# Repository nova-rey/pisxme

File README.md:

# PiSXMe

PiSXMe is an open-hardware compute-appliance carrier project for a Raspberry Pi Compute Module 5 and an NVIDIA Tesla V100 SXM2 module.

This public repository is a recovery/preservation snapshot prepared from verified local source files while the original iCloud-backed checkout contained unavailable File Provider placeholders. It preserves the Rev A design evidence and handoff material; it is not a claim that Rev A is fabrication-ready.

Read [HANDOFF_LINUX_WORKSTATION.md](HANDOFF_LINUX_WORKSTATION.md), [TOOLING_STATUS.md](TOOLING_STATUS.md), [references/REFERENCE_INDEX.md](references/REFERENCE_INDEX.md), and [plans/M6_LINUX_RESTART_CHECKLIST.md](plans/M6_LINUX_RESTART_CHECKLIST.md) before changing the design.

The authoritative active-design hashes and unavailable-source manifest are recorded in [RECOVERY_MANIFEST.md](RECOVERY_MANIFEST.md).

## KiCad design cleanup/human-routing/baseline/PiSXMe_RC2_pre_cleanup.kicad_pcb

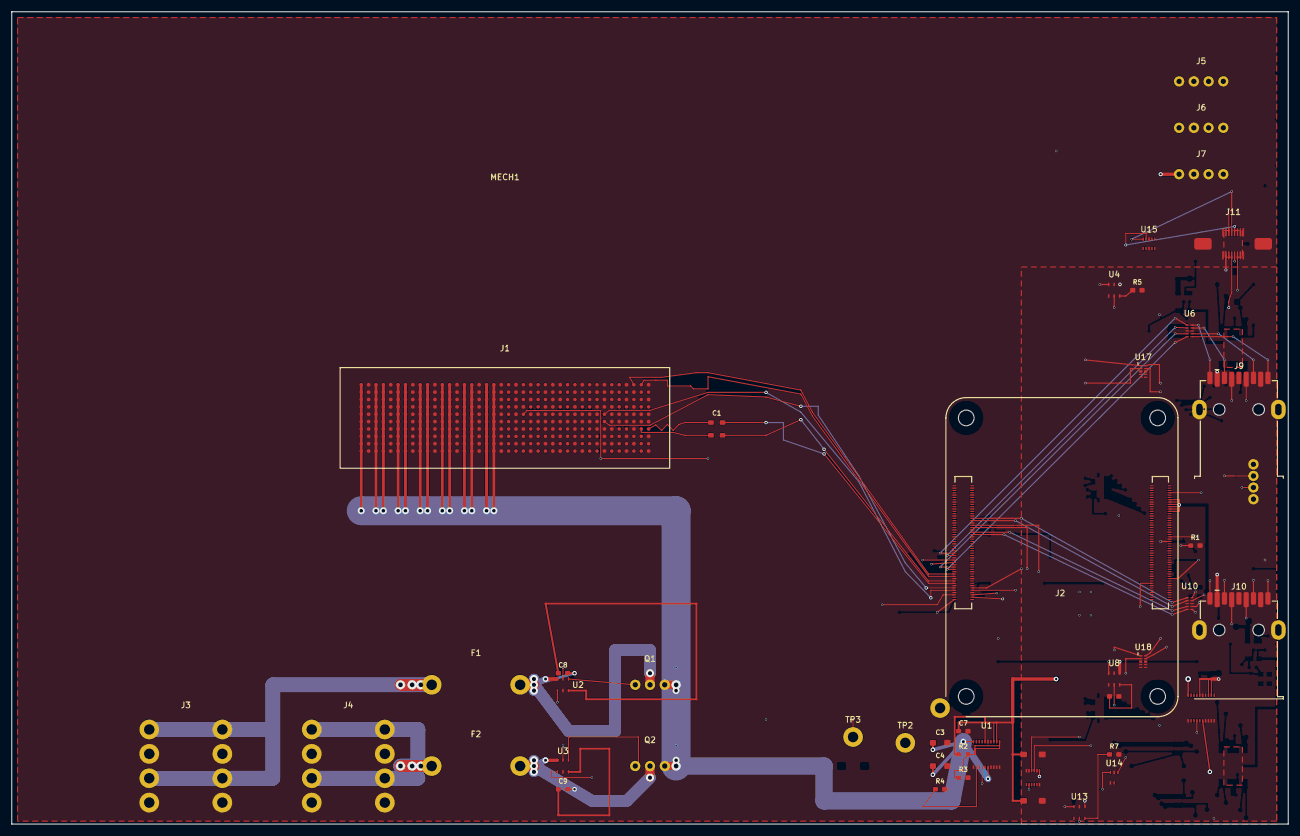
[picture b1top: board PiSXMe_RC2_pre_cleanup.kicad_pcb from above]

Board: 6 copper layers, 220.0 x 140.0 mm, 49 parts (0 on the bottom side), 56 nets.

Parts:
C1, C2: GRM21BR71H224KA01# 220nF; ROUT_0805
C3, C4: 10uF 50V buck input; ROUT_1206
C5, C6: 22uF 25V buck output; ROUT_1210
C7: 100nF VLDOIN; ROUT_0603
C8: 100nF LM74700 VCAP A; ROUT_0603
C9: 100nF LM74700 VCAP B; ROUT_0603
F1, F2: Littelfuse 178.6165.0001 / 0297015.U 15A holder; ATO_FuseHolder
J1: 74221-101LF; SXM2_74221-101LF
J2: 2x 10164227-1004A1RLF; CM5_1004
J3, J4: Molex 39301082 / Mini-Fit Jr 8-circuit; MiniFitJr_8_RA
J5: Molex 22-23-2041 / PC PWM fan 1; Fan_2x2_2.54mm
J6: Molex 22-23-2041 / PC PWM fan 2; Fan_2x2_2.54mm
J7: Molex 22-23-2041 / pump or auxiliary fan; Fan_2x2_2.54mm
J8: JST B4B-PH-K-S / CM5 UART; JST_PH_4
J9, J10: USB3_A_Receptacle_Wuerth_692122030100; USB3_A_Wuerth_692122030100
J11: Amphenol 10171746-00021LF USB-C USB2 SERVICE; USB_C_SERVICE_10171746
MECH1: V100/SXM2 module envelope only; V100_MODULE_ENVELOPE
Q1, Q2: CSD19536KCS 100V 2.7mΩ N-MOSFET; CSD19536KCS_TO220
R1: 0R CLKREQ link DNP/POP; ROUT_0603
R2: 40.2k buck feedback; ROUT_0603
R3: 10.0k buck feedback; ROUT_0603
R4: 13.0k buck RT; ROUT_0603
R5: 16.9k 1% TPS2553 ILIM FAST A; ROUT_0603
R6: 16.9k 1% TPS2553 ILIM FAST B; ROUT_0603
R7: 52.3k TPS2553 ILIM; ROUT_0603
TP1: PERST# test point; TestPoint
TP2: REFCLK access marker (no probe stub); TestPoint
TP3: CM5 nRPIBOOT / internal recovery test point; TestPoint
U1: TPSM63606RDLR 12V-to-5V 6A module; TPSM63606
U2, U3: LM74700QDBVRQ1 reverse-polarity controller; LM74700_DBV
U4: TPS2553DBVR FAST A USB3 Type-A VBUS current limit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; TPS2553_DBV
U6: TPD4EUSB30 SuperSpeed ESD FAST A 1; TPD4E05U06_DQA_TI_FLOWTHROUGH
U8: TPS2553DBVR FAST B USB3 Type-A VBUS current limit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; TPS2553_DBV
U10: TPD4EUSB30 SuperSpeed ESD FAST B 1; TPD4E05U06_DQA_TI_FLOWTHROUGH
U12: TUSB320LAIRWBR USB-C DRP controller SERVICE; TUSB320LAI_RWB
U13: TPS2553DBVR USB2 SERVICE current limiter; TPS2553_DBV
U14: SN74LVC1G04DCKR SERVICE VBUS role inverter; SN74LVC1G04_DCK
U15: TPD2EUSB30A USB2 ESD SERVICE; TPD2EUSB30A_DQA
U16: TPSM63606RDLR dedicated USB 5V peripheral rail; TPSM63606_USB
U17, U18: TPD2EUSB30A USB2 companion ESD; TPD2EUSB30A_DQA_TI_FLOWTHROUGH

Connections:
/3V3: J2.84, J2.86, J8.4, U12.5, U12.12, U14.4
/CM5_5V: C5.1, C6.1, C7.1, J2.77, J2.79, J2.81, J2.83, J2.85, J2.87, R2.1, U1.5, U1.8, U1.9
/CM5_5V_FB: R2.2, R3.1, U1.10
/CM5_CLKREQ_N: J2.102, R1.1
/CM5_USB3_0_RX_N: J2.128, J9.5, U6.5, U6.6
/CM5_USB3_0_RX_P: J2.130, J9.6, U6.4, U6.7
/CM5_USB3_0_TX_N: J2.140, J9.8, U6.2, U6.9
/CM5_USB3_0_TX_P: J2.142, J9.9, U6.1, U6.10
/CM5_USB3_1_RX_N: J2.157, J10.5, U10.5, U10.6
/CM5_USB3_1_RX_P: J2.159, J10.6, U10.4, U10.7
/CM5_USB3_1_TX_N: J2.169, J10.8, U10.2, U10.9
/CM5_USB3_1_TX_P: J2.171, J10.9, U10.1, U10.10
/CM5_VBUS_EN: J2.111, U4.5, U8.5
/CM5_nRPIBOOT: J2.93, TP3.1
/FAN_PWM: J2.19, J5.4, J6.4, J7.4
/FAN_TACH: J2.16, J5.3, J6.3, J7.3
/FUSED_A_12V: C8.2, F1.2, Q1.2, U2.1
/FUSED_B_12V: C9.2, F2.2, Q2.2, U3.1
/GATE_A: Q1.1, U2.3
/GATE_B: Q2.1, U3.3
/GND: C3.2, C4.2, C5.2, C6.2, C7.2, J1.A1, J1.A4, J1.A7, J1.A10, J1.A13, J1.A14, J1.A17, J1.A19, J1.A21, J1.A24, J1.A27, J1.A30, J1.A33, J1.A36, J1.A39, J1.B3, J1.B6, J1.B7, J1.B8, J1.B11, J1.B14, J1.B15, J1.B18, J1.B19, J1.B21, J1.B24, J1.B27, J1.B30, J1.B33, J1.B36, J1.B39, J1.C1, J1.C4, J1.C7, J1.C10, J1.C13, J1.C14, J1.C17, J1.C19, J1.C21, J1.C24, J1.C27, J1.C30, J1.C33, J1.C36, J1.C39, J1.D3, J1.D6, J1.D7, J1.D8, J1.D11, J1.D14, J1.D15, J1.D18, J1.D19, J1.D21, J1.D24, J1.D27, J1.D30, J1.D33, J1.D36, J1.D39, J1.E1, J1.E2, J1.E3, J1.E4, J1.E5, J1.E6, J1.E8, J1.E9, J1.E10, J1.E11, J1.E12, J1.E13, J1.E14, J1.E15, J1.E16, J1.E17, J1.E19, J1.E21, J1.E24, J1.E27, J1.E30, J1.E33, J1.E36, J1.E39, J1.F1, J1.F2, J1.F3, J1.F4, J1.F5, J1.F6, J1.F8, J1.F9, J1.F10, J1.F11, J1.F12, J1.F13, J1.F14, J1.F15, J1.F16, J1.F17, J1.F19, J1.F21, J1.F24, J1.F27, J1.F30, J1.F33, J1.F36, J1.F39, J1.G3, J1.G6, J1.G7, J1.G8, J1.G11, J1.G14, J1.G15, J1.G18, J1.G19, J1.G21, J1.G24, J1.G27, J1.G30, J1.G33, J1.G36, J1.G39, J1.H1, J1.H4, J1.H7, J1.H10, J1.H13, J1.H14, J1.H17, J1.H21, J1.H24, J1.H27, J1.H30, J1.H33, J1.H36, J1.H39, J1.J3, J1.J6, J1.J7, J1.J8, J1.J11, J1.J14, J1.J15, J1.J18, J1.J19, J1.J21, J1.J24, J1.J27, J1.J30, J1.J33, J1.J36, J1.J39, J1.K1, J1.K4, J1.K7, J1.K10, J1.K13, J1.K14, J1.K17, J1.K21, J1.K24, J1.K27, J1.K30, J1.K33, J1.K36, J1.K39, J2.1, J2.2, J2.7, J2.8, J2.13, J2.14, J2.22, J2.23, J2.32, J2.33, J2.42, J2.43, J2.52, J2.53, J2.59, J2.60, J2.65, J2.66, J2.71, J2.74, J2.98, J2.107, J2.108, J2.113, J2.114, J2.119, J2.120, J2.125, J2.126, J2.131, J2.132, J2.137, J2.138, J2.144, J2.150, J2.155, J2.156, J2.161, J2.162, J2.167, J2.168, J2.173, J2.174, J2.179, J2.180, J2.185, J2.186, J2.191, J2.192, J2.197, J2.198, J3.2, J3.4, J3.6, J3.8, J4.2, J4.4, J4.6, J4.8, J5.2, J6.2, J7.2, J8.1, J9.4, J9.7, J9.SH, J10.4, J10.7, J10.SH, J11.A1, J11.A12, J11.B1, J11.B12, J11.S1, J11.S2, R1.2, R3.2, R4.2, R5.2, R6.2, R7.2, U1.6, U1.11, U1.17, U1.18, U1.19, U1.20, U2.5, U3.5, U4.2, U6.3, U6.8, U8.2, U10.3, U10.8, U12.1, U12.2, U13.2, U14.2, U15.3, U15.8, U16.6, U16.11, U16.17, U16.18, U16.19, U16.20, U17.3, U17.8, U18.3, U18.8
/PCIE_PWR_EN: J2.106, U1.14, U2.4, U3.4, U16.14
/PER0_N: J1.A3, J2.124
/PER0_P: J1.A2, J2.122
/PERST_N: J1.E18, J2.109
/PET0_N: C2.2, J2.118
/PET0_N_RAW: C2.1, J1.G2
/PET0_P: C1.2, J2.116
/PET0_P_RAW: C1.1, J1.G1
/RAW_A_12V: F1.1, J3.1, J3.3, J3.5, J3.7
/RAW_B_12V: F2.1, J4.1, J4.3, J4.5, J4.7
/REFCLK_N: J1.F7, J2.112
/REFCLK_P: J1.E7, J2.110
/RT_1MHZ: R4.1, U1.12
/SERVICE_ID_STATUS: U12.8, U14.1
/SERVICE_ILIM: R7.1, U13.6
/SERVICE_VBUS: J11.A4, J11.A9, J11.B4, J11.B9, U12.6, U13.3
/SERVICE_VBUS_EN: U13.5, U14.3
/UART_RX: J2.51, J8.3
/UART_TX: J2.55, J8.2
/USB_5V_PERIPH: U4.1, U8.1, U13.1, U16.5, U16.8, U16.9
/USB_FAST_A_DM: J2.136, J9.2, U17.2, U17.9
/USB_FAST_A_DP: J2.134, J9.3, U17.1, U17.10
/USB_FAST_A_ILIM: R5.1, U4.6
/USB_FAST_A_VBUS: J9.1, U4.3
/USB_FAST_B_DM: J2.165, J10.2, U18.2, U18.9
/USB_FAST_B_DP: J2.163, J10.3, U18.1, U18.10
/USB_FAST_B_ILIM: R6.1, U8.6
/USB_FAST_B_VBUS: J10.1, U8.3
/USB_SERVICE_CC1: J11.A5, U12.3
/USB_SERVICE_CC2: J11.B5, U12.4
/USB_SERVICE_DM: J2.103, J11.A7, J11.B7, U15.2
/USB_SERVICE_DP: J2.105, J11.A6, J11.B6, U15.1
/VCAP_A: C8.1, U2.6
/VCAP_B: C9.1, U3.6
/VPROT_12V: C3.1, C4.1, J1.A22, J1.A23, J1.A25, J1.A26, J1.A28, J1.A29, J1.A31, J1.A32, J1.A34, J1.A35, J1.A37, J1.A38, J1.A40, J1.B22, J1.B23, J1.B25, J1.B26, J1.B28, J1.B29, J1.B31, J1.B32, J1.B34, J1.B35, J1.B37, J1.B38, J1.B40, J1.C22, J1.C23, J1.C25, J1.C26, J1.C28, J1.C29, J1.C31, J1.C32, J1.C34, J1.C35, J1.C37, J1.C38, J1.C40, J1.D22, J1.D23, J1.D25, J1.D26, J1.D28, J1.D29, J1.D31, J1.D32, J1.D34, J1.D35, J1.D37, J1.D38, J1.D40, J1.E22, J1.E23, J1.E25, J1.E26, J1.E28, J1.E29, J1.E31, J1.E32, J1.E34, J1.E35, J1.E37, J1.E38, J1.E40, J1.F22, J1.F23, J1.F25, J1.F26, J1.F28, J1.F29, J1.F31, J1.F32, J1.F34, J1.F35, J1.F37, J1.F38, J1.F40, J1.G22, J1.G23, J1.G25, J1.G26, J1.G28, J1.G29, J1.G31, J1.G32, J1.G34, J1.G35, J1.G37, J1.G38, J1.G40, J1.H22, J1.H23, J1.H25, J1.H26, J1.H28, J1.H29, J1.H31, J1.H32, J1.H34, J1.H35, J1.H37, J1.H38, J1.H40, J1.J22, J1.J23, J1.J25, J1.J26, J1.J28, J1.J29, J1.J31, J1.J32, J1.J34, J1.J35, J1.J37, J1.J38, J1.J40, J1.K22, J1.K23, J1.K25, J1.K26, J1.K28, J1.K29, J1.K31, J1.K32, J1.K34, J1.K35, J1.K37, J1.K38, J1.K40, J5.1, J6.1, J7.1, Q1.3, Q2.3, U1.1, U1.16, U2.2, U3.2, U16.1, U16.16

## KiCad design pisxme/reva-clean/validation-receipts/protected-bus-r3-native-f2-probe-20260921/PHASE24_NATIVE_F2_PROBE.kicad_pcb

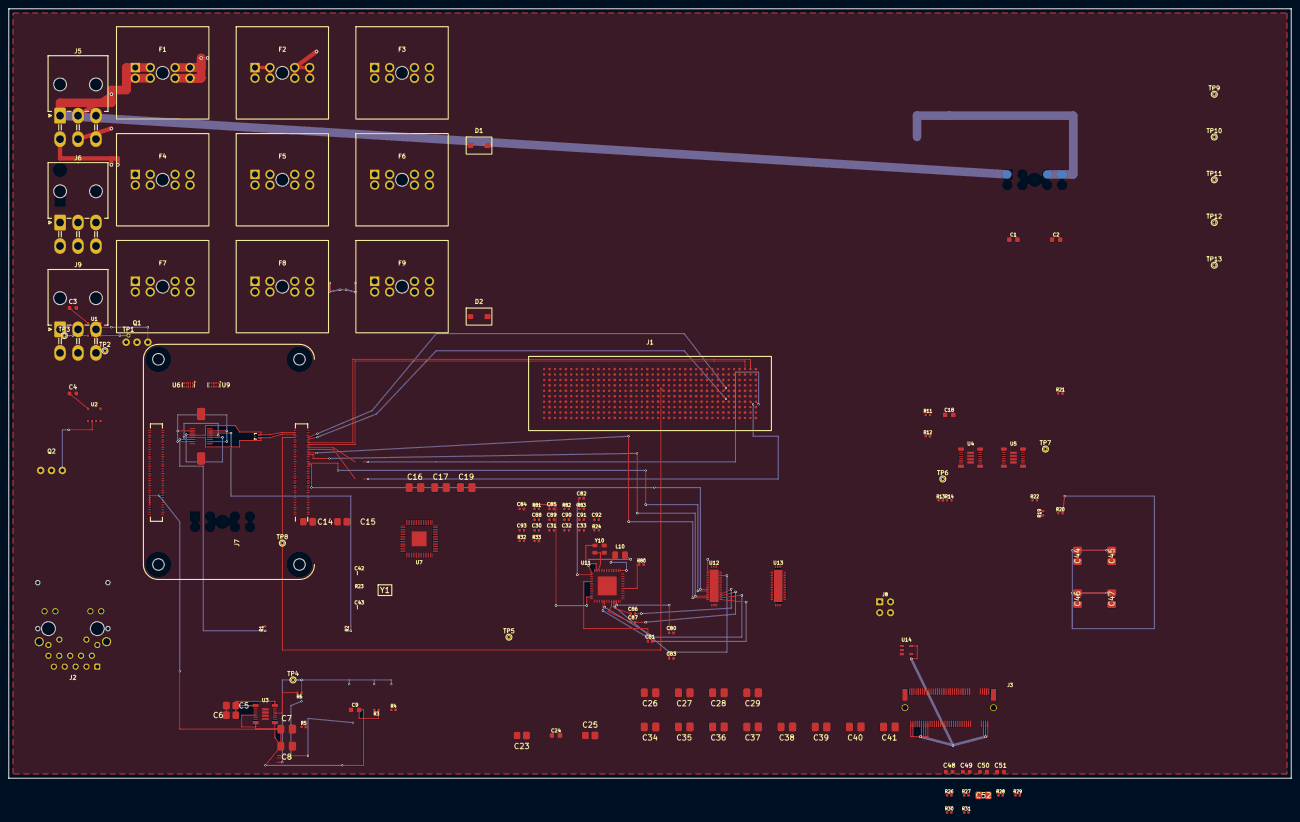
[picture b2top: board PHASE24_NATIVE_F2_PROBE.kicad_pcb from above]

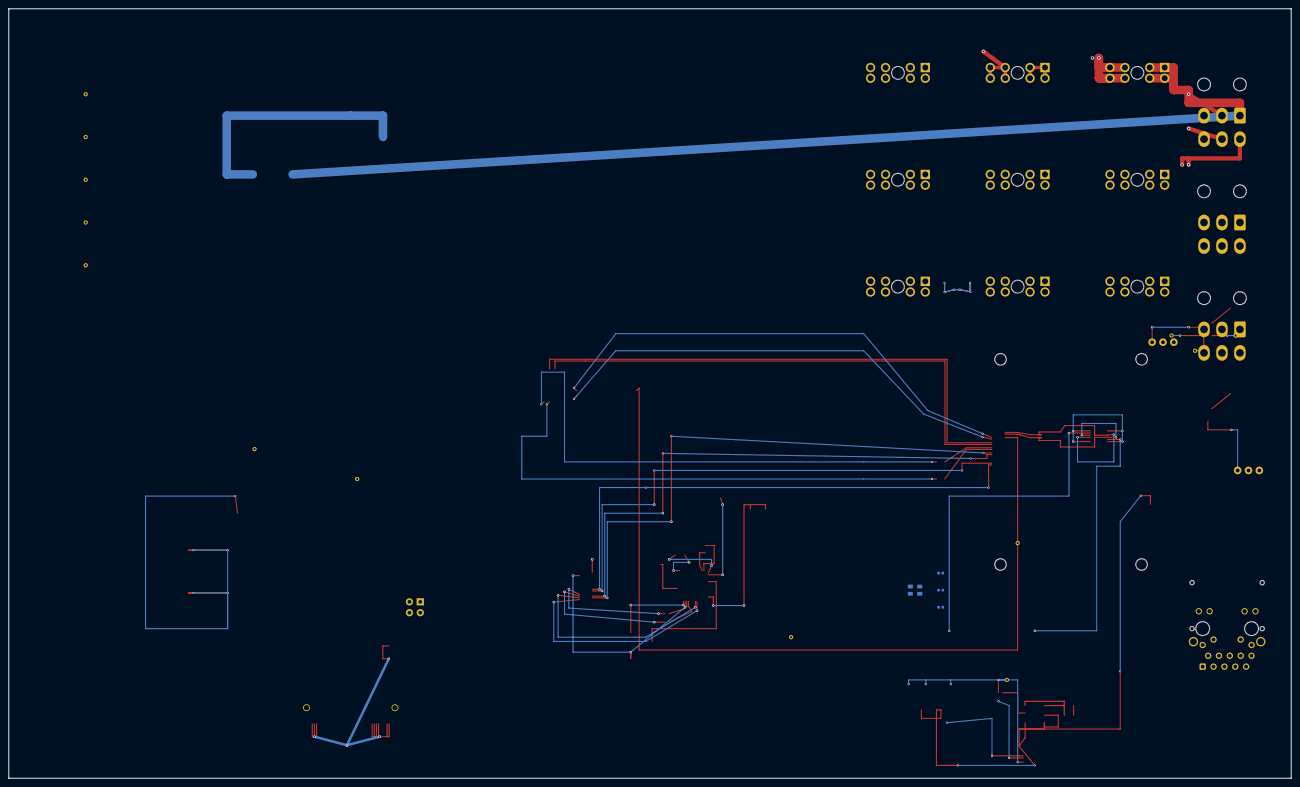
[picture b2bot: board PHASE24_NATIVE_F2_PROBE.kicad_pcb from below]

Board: 6 copper layers, 300.0 x 180.0 mm, 141 parts (17 on the bottom side), 154 nets.

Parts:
C1, C2, C9, C18, C24: C_0805_2012Metric
C3, C4, C48, C49, C50, C51: C_0603_1608Metric
C5, C6, C14, C15, C23, C25, C52: C_1206_3216Metric
C7, C8, C16, C17, C19, C26, C27, C28, C29, C34, C35, C36, C37, C38, C39, C40, C41, C44, C45, C46, C47: C_1210_3225Metric
C30, C31, C32, C33, C42, C43, C80, C81, C82, C83, C84, C85, C86, C87, C88, C89, C90, C91, C92, C93: C_0402_1005Metric
D1, D2: SMBJ18A; TVS_SMBJ18A_DO214AA
F1, F2, F3, F4, F5, F6, F7, F8, F9: 178.6165.0001; ATO_FuseHolder_17861650001
J1: 74221-101LF; PiSXMeRevAClean_SXM2_74221_101LF
J2: A70-112-331N126; EDAC_A70_112_331N126
J3: 1-2199230-4; TE_1-2199230-4_MKEY
J4: Amphenol 10171746-00021LF USB-C USB2 SERVICE; USB_C_SERVICE_10171746
J5, J6, J9: Molex_Mini-Fit_Jr_5569-06A2_2x03_P4.20mm_Horizont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; Molex_5569-06A2_2x03_P4.20mm_Horizontal
J7: Raspberry-Pi-5-Compute-Module; PiSXMeRevAClean_Raspberry_Pi_5_Compute_Module
J8: MODE_JUMPER_1x04
L10: 4.7uH; L_2520_6332Metric
MECH_M2_2280: TE 1-2199230-4 M-key / 2280 full card envelope; M2_2280_RETENTION_ENVELOPE
MECH_M2_2280_CARD_BODY: TE 1-2199230-4 M-key / 2280 card-body no-go
MECH_M2_2280_CONNECTOR_MATING: TE 1-2199230-4 M-key connector mating volume
Q1, Q2: CSD19536KCS; CSD19536KCS_TO220
R1, R2, R3, R4, R5, R6, R11, R12, R13, R14, R19, R20, R21, R22, R23, R24, R26, R27, R28, R29, R30, R31, R32, R33, R80, R81, R82, R83: R_0402_1005Metric
TP1, TP2, TP3, TP4, TP5, TP6, TP7, TP8, TP9, TP10, TP11, TP12, TP13: REV_A_PROBE; TestPoint_THTPad_D1.0mm_Drill0.5mm
U1, U2: LM74700QDBVRQ1; LM74700QDBVRQ1_SOT23_6
U3, U4, U5: TPSM63606RDLR; TPSM63606RDLR_RDL0020
U6, U9: TPD4EUSB30; USON-10_2.5x1.0mm_P0.5mm
U7: TUSB9261IPVP; TUSB9261IPVP_PVP0064A
U8: Texas_DRT_3
U11: JMS583_QFN64_8x8
U12: HD3SS6126_RUA0042A
U13: HD3SS3412_RUA0042A
U14: SOT-23-5
Y1: Crystal_3225_4Pad
Y10: 25MHz; Crystal_3225_4Pad

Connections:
12V_IN_A: C3.2, TP1.1, U1.3
12V_IN_B: C4.2, U2.3
12V_PROTECTED: C5.1, C6.1, C14.1, C15.1, C23.1, C24.1, C25.1, J1.A22, J1.A23, J1.A25, J1.A26, J1.A28, J1.A29, J1.A31, J1.A32, J1.A34, J1.A35, J1.A37, J1.A38, J1.A40, J1.B22, J1.B23, J1.B25, J1.B26, J1.B28, J1.B29, J1.B31, J1.B32, J1.B34, J1.B35, J1.B37, J1.B38, J1.B40, J1.C22, J1.C23, J1.C25, J1.C26, J1.C28, J1.C29, J1.C31, J1.C32, J1.C34, J1.C35, J1.C37, J1.C38, J1.C40, J1.D22, J1.D23, J1.D25, J1.D26, J1.D28, J1.D29, J1.D31, J1.D32, J1.D34, J1.D35, J1.D37, J1.D38, J1.D40, J1.E22, J1.E23, J1.E25, J1.E26, J1.E28, J1.E29, J1.E31, J1.E32, J1.E34, J1.E35, J1.E37, J1.E38, J1.E40, J1.F22, J1.F23, J1.F25, J1.F26, J1.F28, J1.F29, J1.F31, J1.F32, J1.F34, J1.F35, J1.F37, J1.F38, J1.F40, J1.G22, J1.G23, J1.G25, J1.G26, J1.G28, J1.G29, J1.G31, J1.G32, J1.G34, J1.G35, J1.G37, J1.G38, J1.G40, J1.H22, J1.H23, J1.H25, J1.H26, J1.H28, J1.H29, J1.H31, J1.H32, J1.H34, J1.H35, J1.H37, J1.H38, J1.H40, J1.J22, J1.J23, J1.J25, J1.J26, J1.J28, J1.J29, J1.J31, J1.J32, J1.J34, J1.J35, J1.J37, J1.J38, J1.J40, J1.K22, J1.K23, J1.K25, J1.K26, J1.K28, J1.K29, J1.K31, J1.K32, J1.K34, J1.K35, J1.K37, J1.K38, J1.K40, Q1.2, Q2.2, TP3.1, U1.4, U2.4, U3.1, U3.14, U3.16, U4.1, U4.14, U4.16, U5.1, U5.14, U5.16
AUTO_PEDET: J3.69 (AUTO_PEDET), J8.2 (AUTO_PEDET)
BRIDGE_1V1: C26.1, C27.1, C28.1, C29.1, C34.1, C35.1, C36.1, C37.1, C38.1, C39.1, C40.1, C41.1, C44.1, C45.1, C46.1, C47.1, R19.1, R22.1, U5.5, U5.8, U5.9, U7.1, U7.12, U7.19, U7.32, U7.33, U7.41, U7.47, U7.49, U7.55, U7.61, U7.63
BRIDGE_3V3: C16.1, C17.1, C18.2, C19.1, R11.1, R14.1, TP5.1, U4.5, U4.8, U4.9, U7.7, U7.24, U7.30, U7.31, U7.34, U7.40, U7.48, U7.51, U7.62
BRIDGE_R1: R24.1 (BRIDGE_R1), U7.38
BRIDGE_R1RTN: R24.2 (BRIDGE_R1RTN), U7.39
BRIDGE_SATA_RX_N: C33.2 (BRIDGE_SATA_RX_N), U7.59
BRIDGE_SATA_RX_P: C32.2 (BRIDGE_SATA_RX_P), U7.60
BRIDGE_SATA_TX_N: C31.2 (BRIDGE_SATA_TX_N), U7.56
BRIDGE_SATA_TX_P: C30.2 (BRIDGE_SATA_TX_P), U7.57
BRIDGE_USB_DM: U7.35, U12.32 (BRIDGE_USB_DM)
BRIDGE_USB_DP: U7.36, U12.31 (BRIDGE_USB_DP)
BRIDGE_USB_VBUS: R32.2 (BRIDGE_USB_VBUS), R33.1 (BRIDGE_USB_VBUS), U7.50
BRIDGE_VSSOSC: C42.2, C43.2, U7.53, Y1.2, Y1.4
BRIDGE_XI: C42.1, R23.1, U7.52, Y1.1
BRIDGE_XO: C43.1, R23.2, U7.54, Y1.3
CM5_5V: C7.1, C8.1, C9.2, J7.77, J7.79, J7.81, J7.83, J7.85, J7.87, R3.1, R6.1, R32.1 (CM5_5V), TP4.1, U3.5, U3.8, U3.9
CM5_GBE_TD0_N: J2.2, J7.10, U6.2 (D1-), U6.9
CM5_GBE_TD0_P: J2.1, J7.12, U6.1 (D1+), U6.10
CM5_GBE_TD1_N: J2.6, J7.6, U6.4 (D2+), U6.7
CM5_GBE_TD1_P: J2.3, J7.4, U6.5 (D2-), U6.6
CM5_GBE_TD2_N: J2.8, J7.9, U9.2 (D1-), U9.9
CM5_GBE_TD2_P: J2.7, J7.11, U9.1 (D1+), U9.10
CM5_GBE_TD3_N: J2.10, J7.5, U9.4 (D2+), U9.7
CM5_GBE_TD3_P: J2.9, J7.3, U9.5 (D2-), U9.6
CM5_PER0_N: J1.A3, J7.118
CM5_PER0_P: J1.A2, J7.116
CM5_PERST: J1.E18, J7.109, TP8.1
CM5_PET0_N: C2.1, J7.124
CM5_PET0_P: C1.1, J7.122
CM5_REFCLK_N: J1.F7, J7.112
CM5_REFCLK_P: J1.E7, J7.110
CM5_STORAGE_USB2_DM: J7.136, U12.7 (CM5_STORAGE_USB2_DM)
CM5_STORAGE_USB2_DP: J7.134, U12.8 (CM5_STORAGE_USB2_DP)
CM5_USB3_RX_N: J7.128, U7.42, U12.16 (CM5_USB3_RX_N)
CM5_USB3_RX_P: J7.130, U7.43, U12.15 (CM5_USB3_RX_P)
CM5_USB3_TX_N: J7.140, U7.45, U12.12 (CM5_USB3_TX_N)
CM5_USB3_TX_P: J7.142, U7.46, U12.11 (CM5_USB3_TX_P)
ETH_CT1: C48.1, J2.11
ETH_CT2: C49.1, J2.12
ETH_CT3: C50.1, J2.13
ETH_CT4: C51.1, J2.14
ETH_CT_BRANCH_1: C48.2, R26.1
ETH_CT_BRANCH_2: C49.2, R27.1
ETH_CT_BRANCH_3: C50.2, R28.1
ETH_CT_BRANCH_4: C51.2, R29.1
ETH_CT_COMMON: C52.1, R26.2, R27.2, R28.2, R29.2
ETH_LEDG: J7.15, R31.1
ETH_LEDY: J7.17, R30.1
ETH_POWER: J2.15, J2.17
FB_BRIDGE_1V1: R19.2, R20.1, U5.10
FB_BRIDGE_3V3: C18.1, R11.2, R12.1, U4.10
FB_CM5_5V: C9.1, R3.2, R4.1, U3.10
FUSED_12V_A: D1.1, Q1.1, TP2.1, U1.6
FUSED_12V_B: D2.1, Q2.1, U2.6
GATE_A: Q1.3, U1.5
GATE_B: Q2.3, U2.5
GBE_LED_G_K: J2.18, R31.2
GBE_LED_Y_K: J2.16, R30.2
GBE_SHIELD: C52.2, J2.19, J2.20
JMS_AVDD33: C80.1 (JMS_AVDD33), U11.19 (JMS_AVDD33)
JMS_AVDDL: C83.1 (JMS_AVDDL), J3.20 (JMS_AVDDL), J3.30 (JMS_AVDDL), J3.36 (JMS_AVDDL), J3.40 (JMS_AVDDL), J3.46 (JMS_AVDDL), U11.20 (JMS_AVDDL), U11.25 (JMS_AVDDL), U11.30 (JMS_AVDDL), U11.33 (JMS_AVDDL), U11.36 (JMS_AVDDL), U11.40 (JMS_AVDDL), U11.43 (JMS_AVDDL), U11.46 (JMS_AVDDL), U11.49 (JMS_AVDDL), U12.36 (JMS_AVDDL), U12.40 (JMS_AVDDL), U13.40 (JMS_AVDDL)
JMS_GPIO4_NC: J3.8 (JMS_GPIO4_NC), U11.8 (JMS_GPIO4_NC), U13.8 (JMS_GPIO4_NC)
JMS_PCIE_TXN0: C91.2 (JMS_PCIE_TXN0), U13.33 (JMS_PCIE_TXN0)
JMS_PCIE_TXN1: C93.2 (JMS_PCIE_TXN1), U13.24 (JMS_PCIE_TXN1)
JMS_PCIE_TXP0: C90.2 (JMS_PCIE_TXP0), U13.34 (JMS_PCIE_TXP0)
JMS_PCIE_TXP1: C92.2 (JMS_PCIE_TXP1), U13.25 (JMS_PCIE_TXP1)
JMS_RESET_N: C85.1 (JMS_RESET_N), R81.1 (JMS_RESET_N), U11.15 (JMS_RESET_N)
JMS_REXT: R80.1 (JMS_REXT), U11.39 (JMS_REXT)
JMS_SPI_SCK_DNP: U11.4 (JMS_SPI_SCK_DNP), U12.4 (JMS_SPI_SCK_DNP)
JMS_SPI_SI_DNP: U11.5 (JMS_SPI_SI_DNP), U12.5 (JMS_SPI_SI_DNP)
JMS_SPI_SO_DNP: U11.3 (JMS_SPI_SO_DNP), U12.3 (JMS_SPI_SO_DNP)
JMS_USB3_TXN: C87.2 (JMS_USB3_TXN), U12.24 (JMS_USB3_TXN)
JMS_USB3_TXP: C86.2 (JMS_USB3_TXP), U12.25 (JMS_USB3_TXP)
JMS_VBUS_SENSE: R82.2 (JMS_VBUS_SENSE), R83.1 (JMS_VBUS_SENSE), U11.10 (JMS_VBUS_SENSE)
JMS_VCCK: C82.1 (JMS_VCCK), U11.2 (JMS_VCCK), U11.31 (JMS_VCCK), U11.53 (JMS_VCCK), U12.2 (JMS_VCCK)
JMS_VCCO: C81.1 (JMS_VCCO), J3.6 (JMS_VCCO), J3.32 (JMS_VCCO), U11.6 (JMS_VCCO), U11.11 (JMS_VCCO), U11.32 (JMS_VCCO), U11.56 (JMS_VCCO)
JMS_VDDREG_5V: L10.2 (JMS_VDDREG_5V), U11.1 (JMS_VDDREG_5V), U12.1 (JMS_VDDREG_5V), U14.1 (JMS_VDDREG_5V)
JMS_XAVDDH: C84.1 (JMS_XAVDDH), U11.52 (JMS_XAVDDH)
LXO: L10.1 (LXO), U11.64 (LXO)
M2_PCIE_TXN2: J3.23 (M2_PCIE_TXN2), U13.12 (M2_PCIE_TXN2)
M2_PCIE_TXN3: J3.11 (M2_PCIE_TXN3), U13.16 (M2_PCIE_TXN3)
M2_PCIE_TXP2: J3.25 (M2_PCIE_TXP2), U13.11 (M2_PCIE_TXP2)
M2_PCIE_TXP3: J3.13 (M2_PCIE_TXP3), U13.15 (M2_PCIE_TXP3)
M2_SATA_A_N_PCIE_TXN0: J3.47 (M2_SATA_A_N_PCIE_TXN0), U13.3 (M2_SATA_A_N_PCIE_TXN0)
M2_SATA_A_P_PCIE_TXP0: J3.49 (M2_SATA_A_P_PCIE_TXP0), U13.2 (M2_SATA_A_P_PCIE_TXP0)
M2_SATA_B_N_PCIE_RXP0: J3.43 (M2_SATA_B_N_PCIE_RXP0), U13.7 (M2_SATA_B_N_PCIE_RXP0)
M2_SATA_B_P_PCIE_RXN0: J3.41 (M2_SATA_B_P_PCIE_RXN0), U13.6 (M2_SATA_B_P_PCIE_RXN0)
MODE_IN: J8.4 (MODE_IN), U14.2 (MODE_IN)
NC: U3.15, U4.15, U5.15
NC_18: U12.18 (NC_18), U13.18 (NC_18)
NC_26: J3.26 (NC_26), U13.26 (NC_26)
NC_28: J3.28 (NC_28), U13.28 (NC_28)
NC_39: U12.39 (NC_39), U13.39 (NC_39)
NC_41: U12.41 (NC_41), U13.41 (NC_41)
NC_42: J3.42 (NC_42), U12.42 (NC_42), U13.42 (NC_42)
PCIE_TXN0: C91.1 (PCIE_TXN0), U11.44 (PCIE_TXN0)
PCIE_TXN1: C93.1 (PCIE_TXN1), U11.37 (PCIE_TXN1)
PCIE_TXP0: C90.1 (PCIE_TXP0), U11.45 (PCIE_TXP0)
PCIE_TXP1: C92.1 (PCIE_TXP1), U11.38 (PCIE_TXP1)
PG_BRIDGE_1V1: R22.2, TP7.1, U5.13
PG_BRIDGE_3V3: R14.2, TP6.1, U4.13
PG_CM5_5V: R6.2, U3.13
POWER_GND: C5.2, C6.2, C7.2, C8.2, C14.2, C15.2, C16.2, C17.2, C19.2, C23.2, C24.2, C25.2, C26.2, C27.2, C28.2, C29.2, C34.2, C35.2, C36.2, C37.2, C38.2, C39.2, C40.2, C41.2, C44.2, C45.2, C46.2, C47.2, C80.2 (POWER_GND), C81.2 (POWER_GND), C82.2 (POWER_GND), C83.2 (POWER_GND), C84.2 (POWER_GND), C85.2 (POWER_GND), D1.2, D2.2, J1.A1, J1.A4, J1.A7, J1.A10, J1.A13, J1.A14, J1.A17, J1.A19, J1.A21, J1.A24, J1.A27, J1.A30, J1.A33, J1.A36, J1.A39, J1.B3, J1.B6, J1.B7, J1.B8, J1.B11, J1.B14, J1.B15, J1.B18, J1.B19, J1.B21, J1.B24, J1.B27, J1.B30, J1.B33, J1.B36, J1.B39, J1.C1, J1.C4, J1.C7, J1.C10, J1.C13, J1.C14, J1.C17, J1.C19, J1.C21, J1.C24, J1.C27, J1.C30, J1.C33, J1.C36, J1.C39, J1.D3, J1.D6, J1.D7, J1.D8, J1.D11, J1.D14, J1.D15, J1.D18, J1.D19, J1.D21, J1.D24, J1.D27, J1.D30, J1.D33, J1.D36, J1.D39, J1.E1, J1.E2, J1.E3, J1.E4, J1.E5, J1.E6, J1.E8, J1.E9, J1.E10, J1.E11, J1.E12, J1.E13, J1.E14, J1.E15, J1.E16, J1.E17, J1.E19, J1.E21, J1.E24, J1.E27, J1.E30, J1.E33, J1.E36, J1.E39, J1.F1, J1.F2, J1.F3, J1.F4, J1.F5, J1.F6, J1.F8, J1.F9, J1.F10, J1.F11, J1.F12, J1.F13, J1.F14, J1.F15, J1.F16, J1.F17, J1.F19, J1.F21, J1.F24, J1.F27, J1.F30, J1.F33, J1.F36, J1.F39, J1.G3, J1.G6, J1.G7, J1.G8, J1.G11, J1.G14, J1.G15, J1.G18, J1.G19, J1.G21, J1.G24, J1.G27, J1.G30, J1.G33, J1.G36, J1.G39, J1.H1, J1.H4, J1.H7, J1.H10, J1.H13, J1.H14, J1.H17, J1.H21, J1.H24, J1.H27, J1.H30, J1.H33, J1.H36, J1.H39, J1.J3, J1.J6, J1.J7, J1.J8, J1.J11, J1.J14, J1.J15, J1.J18, J1.J19, J1.J21, J1.J24, J1.J27, J1.J30, J1.J33, J1.J36, J1.J39, J1.K1, J1.K4, J1.K7, J1.K10, J1.K13, J1.K14, J1.K17, J1.K21, J1.K24, J1.K27, J1.K30, J1.K33, J1.K36, J1.K39, J3.3 (POWER_GND), J3.9 (POWER_GND), J3.15 (POWER_GND), J3.27 (POWER_GND), J3.33 (POWER_GND), J3.39 (POWER_GND), J3.45 (POWER_GND), J3.51 (POWER_GND), J3.57 (POWER_GND), J3.71 (POWER_GND), J3.73 (POWER_GND), J7.1, J7.2, J7.7, J7.8, J7.13, J7.14, J7.22, J7.23, J7.32, J7.33, J7.42, J7.43, J7.52, J7.53, J7.59, J7.60, J7.65, J7.66, J7.71, J7.74, J7.98, J7.107, J7.108, J7.113, J7.114, J7.119, J7.120, J7.125, J7.126, J7.131, J7.132, J7.137, J7.138, J7.144, J7.150, J7.155, J7.156, J7.161, J7.162, J7.167, J7.168, J7.173, J7.174, J7.179, J7.180, J7.185, J7.186, J7.191, J7.192, J7.197, J7.198, R4.2, R5.2, R12.2, R13.2, R20.2, R21.2, R33.2 (POWER_GND), R80.2 (POWER_GND), R83.2 (POWER_GND), TP9.1, U1.2, U2.2, U3.6, U3.11, U3.17, U3.18, U3.19, U3.20, U4.6, U4.11, U4.17, U4.18, U4.19, U4.20, U5.6, U5.11, U5.17, U5.18, U5.19, U5.20, U6.3 (GND), U6.8 (GND), U7.44, U7.58, U7.65, U9.3 (GND), U9.8 (GND), U11.60 (POWER_GND), U11.63 (POWER_GND), U12.10 (POWER_GND), U12.14 (POWER_GND), U12.17 (POWER_GND), U12.19 (POWER_GND), U12.21 (POWER_GND), U12.43 (POWER_GND), U13.1 (POWER_GND), U13.4 (POWER_GND), U13.10 (POWER_GND), U13.14 (POWER_GND), U13.17 (POWER_GND), U13.19 (POWER_GND), U13.21 (POWER_GND), U14.3 (POWER_GND), Y10.3 (POWER_GND), Y10.4 (POWER_GND)
PWR_FUSED_J5_P1: F1.5, F1.6, F1.7, F1.8
PWR_FUSED_J5_P2: F2.5, F2.6, F2.7, F2.8
PWR_FUSED_J5_P3: F3.5, F3.6, F3.7, F3.8
PWR_FUSED_J6_P1: F4.5, F4.6, F4.7, F4.8
PWR_FUSED_J6_P2: F5.5, F5.6, F5.7, F5.8
PWR_FUSED_J6_P3: F6.5, F6.6, F6.7, F6.8
PWR_FUSED_J9_P1: F7.5, F7.6, F7.7, F7.8
PWR_FUSED_J9_P2: F8.5, F8.6, F8.7, F8.8
PWR_FUSED_J9_P3: F9.5, F9.6, F9.7, F9.8
PWR_SRC_J5_P1: F1.1, F1.2, F1.3, F1.4, J5.1
PWR_SRC_J5_P2: F2.1, F2.2, F2.3, F2.4, J5.2
PWR_SRC_J5_P3: F3.1, F3.2, F3.3, F3.4, J5.3
PWR_SRC_J6_P1: F4.1, F4.2, F4.3, F4.4, J6.1
PWR_SRC_J6_P2: F5.1, F5.2, F5.3, F5.4, J6.2
PWR_SRC_J6_P3: F6.1, F6.2, F6.3, F6.4, J6.3
PWR_SRC_J9_P1: F7.1, F7.2, F7.3, F7.4, J9.1
PWR_SRC_J9_P2: F8.1, F8.2, F8.3, F8.4, J9.2
PWR_SRC_J9_P3: F9.1, F9.2, F9.3, F9.4, J9.3
RT_BRIDGE_1V1: R21.1, U5.12
RT_BRIDGE_3V3: R13.1, U4.12
RT_CM5_5V: R5.1, U3.12
SERVICE_GND: J4.A1, J4.A12, J4.B1, J4.B12, R1.2, R2.2, U8.3
SERVICE_RD_A: J4.A5, R1.1
SERVICE_RD_B: J4.B5, R2.1
SERVICE_USB2_DM: J4.A7, J4.B7, J7.103, U8.2
SERVICE_USB2_DP: J4.A6, J4.B6, J7.105, U8.1
SERVICE_VBUS_SENSE: J4.A4, J4.A9, J4.B4, J4.B9
STORAGE_3V3: J3.2 (M2_3V3), J3.4 (M2_3V3), J3.12 (M2_3V3), J3.14 (M2_3V3), J3.16 (M2_3V3), J3.18 (M2_3V3), J3.70 (M2_3V3), J3.72 (M2_3V3), J3.74 (M2_3V3), R81.2 (STORAGE_3V3), U12.13 (STORAGE_3V3), U12.20 (STORAGE_3V3), U12.30 (STORAGE_3V3), U13.5 (STORAGE_3V3), U13.13 (STORAGE_3V3), U13.20 (STORAGE_3V3), U13.30 (STORAGE_3V3), U14.5 (STORAGE_3V3)
STORAGE_SEL: U12.9 (STORAGE_SEL), U13.9 (STORAGE_SEL), U14.4 (STORAGE_SEL)
TUSB_SATA_RXN: C33.1 (TUSB_SATA_RXN), U13.35 (TUSB_SATA_RXN)
TUSB_SATA_RXP: C32.1 (TUSB_SATA_RXP), U13.36 (TUSB_SATA_RXP)
TUSB_SATA_TXN: C31.1 (TUSB_SATA_TXN), U13.37 (TUSB_SATA_TXN)
TUSB_SATA_TXP: C30.1 (TUSB_SATA_TXP), U13.38 (TUSB_SATA_TXP)
USB_DM: U11.17 (USB_DM), U12.34 (USB_DM)
USB_DP: U11.18 (USB_DP), U12.33 (USB_DP)
USB_RXN1: U11.27 (USB_RXN1), U12.22 (USB_RXN1)
USB_RXP1: U11.26 (USB_RXP1), U12.23 (USB_RXP1)
USB_TXN1: C87.1 (USB_TXN1), U11.22 (USB_TXN1)
USB_TXN2: C89.1 (USB_TXN2), U11.23 (USB_TXN2)
USB_TXP1: C86.1 (USB_TXP1), U11.21 (USB_TXP1)
USB_TXP2: C88.1 (USB_TXP2), U11.24 (USB_TXP2)
V100_PET0_N: C2.2, J1.G2
V100_PET0_P: C1.2, J1.G1
VBUS: R82.1 (VBUS), U11.16 (VBUS)
VCAP_A: C3.1, U1.1
VCAP_B: C4.1, U2.1
XIN: U11.50 (XIN), Y10.1 (XIN)
XOUT: U11.51 (XOUT), Y10.2 (XOUT)

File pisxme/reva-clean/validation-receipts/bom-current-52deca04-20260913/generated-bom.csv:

"Refs","Value","Footprint","Qty","DNP"
"C1","220nF X7R 50V","Capacitor_SMD:C_0805_2012Metric","1",""
"C2","220nF X7R 50V","Capacitor_SMD:C_0805_2012Metric","1",""
"C3","100nF VCAP A","PiSXMeRevAClean:C_0603_1608Metric","1",""
"C4","100nF VCAP B","PiSXMeRevAClean:C_0603_1608Metric","1",""
"C5","10uF 50V","PiSXMeRevAClean:C_1206_3216Metric","1",""
"C6","10uF 50V","PiSXMeRevAClean:C_1206_3216Metric","1",""
"C7","22uF","PiSXMeRevAClean:C_1210_3225Metric","1",""
"C8","22uF","PiSXMeRevAClean:C_1210_3225Metric","1",""
"C9","22pF","PiSXMeRevAClean:C_0805_2012Metric","1",""
"C14","10uF 50V","PiSXMeRevAClean:C_1206_3216Metric","1",""
"C15","10uF 50V","PiSXMeRevAClean:C_1206_3216Metric","1",""
"C16","22uF","PiSXMeRevAClean:C_1210_3225Metric","1",""
"C17","22uF","PiSXMeRevAClean:C_1210_3225Metric","1",""
"C18","47pF","PiSXMeRevAClean:C_0805_2012Metric","1",""
"C19","22uF","PiSXMeRevAClean:C_1210_3225Metric","1",""
"C23","10uF 50V","PiSXMeRevAClean:C_1206_3216Metric","1",""
"C24","1uF","PiSXMeRevAClean:C_0805_2012Metric","1",""
"C25","10uF 50V","PiSXMeRevAClean:C_1206_3216Metric","1",""
"C26","22uF","PiSXMeRevAClean:C_1210_3225Metric","1",""
"C27","22uF","PiSXMeRevAClean:C_1210_3225Metric","1",""
"C28","22uF","PiSXMeRevAClean:C_1210_3225Metric","1",""
"C29","22uF","PiSXMeRevAClean:C_1210_3225Metric","1",""
"C30","100nF","PiSXMeRevAClean:C_0402_1005Metric","1",""
"C31","100nF","PiSXMeRevAClean:C_0402_1005Metric","1",""
"C32","100nF","PiSXMeRevAClean:C_0402_1005Metric","1",""
"C33","100nF","PiSXMeRevAClean:C_0402_1005Metric","1",""
"C34","22uF","PiSXMeRevAClean:C_1210_3225Metric","1",""
"C35","22uF","PiSXMeRevAClean:C_1210_3225Metric","1",""
"C36","22uF","PiSXMeRevAClean:C_1210_3225Metric","1",""
"C37","22uF","PiSXMeRevAClean:C_1210_3225Metric","1",""
"C38","22uF","PiSXMeRevAClean:C_1210_3225Metric","1",""
"C39","22uF","PiSXMeRevAClean:C_1210_3225Metric","1",""
"C40","22uF","PiSXMeRevAClean:C_1210_3225Metric","1",""
"C41","22uF","PiSXMeRevAClean:C_1210_3225Metric","1",""
"C42","18pF","PiSXMeRevAClean:C_0402_1005Metric","1",""
"C43","18pF","PiSXMeRevAClean:C_0402_1005Metric","1",""
"C44","22uF","PiSXMeRevAClean:C_1210_3225Metric","1",""
"C45","22uF","PiSXMeRevAClean:C_1210_3225Metric","1",""
"C46","22uF","PiSXMeRevAClean:C_1210_3225Metric","1",""
"C47","22uF","PiSXMeRevAClean:C_1210_3225Metric","1",""
"C48","22nF 100V","PiSXMeRevAClean:C_0603_1608Metric","1",""
"C49","22nF 100V","PiSXMeRevAClean:C_0603_1608Metric","1",""
"C50","22nF 100V","PiSXMeRevAClean:C_0603_1608Metric","1",""
"C51","22nF 100V","PiSXMeRevAClean:C_0603_1608Metric","1",""
"C52","1nF 2kV","PiSXMeRevAClean:C_1206_3216Metric","1",""
"C80","4.7uF","PiSXMeRevAClean:C_0603_1608Metric","1",""
"C81","100n","PiSXMeRevAClean:C_0402_1005Metric","1",""
"C82","100n","PiSXMeRevAClean:C_0402_1005Metric","1",""
"C83","100n","PiSXMeRevAClean:C_0402_1005Metric","1",""
"C84","100n","PiSXMeRevAClean:C_0402_1005Metric","1",""
"C85","100n reset delay","PiSXMeRevAClean:C_0402_1005Metric","1",""
"C86","100n USB TX1P","PiSXMeRevAClean:C_0402_1005Metric","1",""
"C87","100n USB TX1N","PiSXMeRevAClean:C_0402_1005Metric","1",""
"C88","100n USB TX2P","PiSXMeRevAClean:C_0402_1005Metric","1",""
"C89","100n USB TX2N","PiSXMeRevAClean:C_0402_1005Metric","1",""
"C90","220n PCIe TX0P","PiSXMeRevAClean:C_0402_1005Metric","1",""
"C91","220n PCIe TX0N","PiSXMeRevAClean:C_0402_1005Metric","1",""
"C92","220n PCIe TX1P","PiSXMeRevAClean:C_0402_1005Metric","1",""
"C93","220n PCIe TX1N","PiSXMeRevAClean:C_0402_1005Metric","1",""
"D1","SMBJ18A","PiSXMeRevAClean:TVS_SMBJ18A_DO214AA","1",""
"D2","SMBJ18A","PiSXMeRevAClean:TVS_SMBJ18A_DO214AA","1",""
"F1","0297015.U / 178.6165.0001","PiSXMeRevAClean:ATO_FuseHolder_17861650001","1",""
"F2","0297015.U / 178.6165.0001","PiSXMeRevAClean:ATO_FuseHolder_17861650001","1",""
"J1","Amphenol 74221-101LF Rev-W","PiSXMeRevAClean:PiSXMeRevAClean_SXM2_74221_101LF","1",""
"J2","A70-112-331N126","PiSXMeRevAClean:EDAC_A70_112_331N126","1",""
"J3","1-2199230-4","PiSXMeRevAClean:TE_1-2199230-4_MKEY","1",""
"J4","10171746-00021LF","PiSXMeRevAClean:USB_C_SERVICE_10171746","1",""
"J5","0039300020","PiSXMeRevAClean:Molex_0039300020_5569_2P_RA","1",""
"J6","0039300020","PiSXMeRevAClean:Molex_0039300020_5569_2P_RA","1",""
"J7","ComputeModule5-CM5","PiSXMeRevAClean:PiSXMeRevAClean_Raspberry_Pi_5_Compute_Module","1",""
"J8","AUTO / FORCE SATA / FORCE NVMe","PiSXMeRevAClean:MODE_JUMPER_1x04","1",""
"L10","4.7uH","PiSXMeRevAClean:L_2520_6332Metric","1",""
"Q1","CSD19536KCS","PiSXMeRevAClean:CSD19536KCS_TO220","1",""
"Q2","CSD19536KCS","PiSXMeRevAClean:CSD19536KCS_TO220","1",""
"R1","5.1k Rd","PiSXMeRevAClean:R_0402_1005Metric","1",""
"R2","5.1k Rd","PiSXMeRevAClean:R_0402_1005Metric","1",""
"R3","40.2k","PiSXMeRevAClean:R_0402_1005Metric","1",""
"R4","10k","PiSXMeRevAClean:R_0402_1005Metric","1",""
"R5","13k","PiSXMeRevAClean:R_0402_1005Metric","1",""
"R6","100k","PiSXMeRevAClean:R_0402_1005Metric","1",""
"R11","23.2k","PiSXMeRevAClean:R_0402_1005Metric","1",""
"R12","10k","PiSXMeRevAClean:R_0402_1005Metric","1",""
"R13","27k","PiSXMeRevAClean:R_0402_1005Metric","1",""
"R14","100k","PiSXMeRevAClean:R_0402_1005Metric","1",""
"R19","1k","PiSXMeRevAClean:R_0402_1005Metric","1",""
"R20","10k","PiSXMeRevAClean:R_0402_1005Metric","1",""
"R21","2k","PiSXMeRevAClean:R_0402_1005Metric","1",""
"R22","100k","PiSXMeRevAClean:R_0402_1005Metric","1",""
"R23","1M","PiSXMeRevAClean:R_0402_1005Metric","1",""
"R24","10K","PiSXMeRevAClean:R_0402_1005Metric","1",""
"R26","75R","PiSXMeRevAClean:R_0402_1005Metric","1",""
"R27","75R","PiSXMeRevAClean:R_0402_1005Metric","1",""
"R28","75R","PiSXMeRevAClean:R_0402_1005Metric","1",""
"R29","75R","PiSXMeRevAClean:R_0402_1005Metric","1",""
"R30","470R","PiSXMeRevAClean:R_0402_1005Metric","1",""
"R31","470R","PiSXMeRevAClean:R_0402_1005Metric","1",""
"R32","90.9K","PiSXMeRevAClean:R_0402_1005Metric","1",""
"R33","10K","PiSXMeRevAClean:R_0402_1005Metric","1",""
"R80","12k 1%","PiSXMeRevAClean:R_0402_1005Metric","1",""
"R81","10k reset pullup","PiSXMeRevAClean:R_0402_1005Metric","1",""
"R82","100k VBUS top","PiSXMeRevAClean:R_0402_1005Metric","1",""
"R83","100k VBUS bottom","PiSXMeRevAClean:R_0402_1005Metric","1",""
"U1","LM74700QDBVRQ1","PiSXMeRevAClean:LM74700QDBVRQ1_SOT23_6","1",""
"U2","LM74700QDBVRQ1","PiSXMeRevAClean:LM74700QDBVRQ1_SOT23_6","1",""
"U3","TPSM63606RDLR","PiSXMeRevAClean:TPSM63606RDLR_RDL0020","1",""
"U4","TPSM63606RDLR","PiSXMeRevAClean:TPSM63606RDLR_RDL0020","1",""
"U5","TPSM63606RDLR","PiSXMeRevAClean:TPSM63606RDLR_RDL0020","1",""
"U6","TPD4EUSB30DQAR","PiSXMeRevAClean:USON-10_2.5x1.0mm_P0.5mm","1",""
"U7","TUSB9261IPVP","PiSXMeRevAClean:TUSB9261IPVP_PVP0064A","1",""
"U8","TPD2EUSB30DRTR","PiSXMeRevAClean:Texas_DRT_3","1",""
"U9","TPD4EUSB30DQAR","PiSXMeRevAClean:USON-10_2.5x1.0mm_P0.5mm","1",""
"U11","JMS583-QHFA3A","PiSXMeRevAClean:JMS583_QFN64_8x8","1",""
"U12","HD3SS6126RUAR","PiSXMeRevAClean:HD3SS6126_RUA0042A","1",""
"U13","HD3SS3412RUAR","PiSXMeRevAClean:HD3SS3412_RUA0042A","1",""
"U14","SN74LVC1G17DBVR","Package_TO_SOT_SMD:SOT-23-5","1",""
"Y1","ECS-400-18-33-JGN-TR3","PiSXMeRevAClean:Crystal_3225_4Pad","1",""
"Y10","25MHz +/-30ppm","PiSXMeRevAClean:Crystal_3225_4Pad","1",""

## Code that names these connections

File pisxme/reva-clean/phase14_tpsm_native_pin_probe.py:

"""Probe the proven KiCad right-facing pin/label serialization for TPSM."""
from pathlib import Path
from phase3_scaffold import balanced

P=Path(__file__).resolve().parent/'REGULATORS.kicad_sch'
N={1:'VIN1',2:'SW',3:'CBOOT',4:'RBOOT',5:'VLDOIN',6:'AGND',7:'VCC',8:'VOUT1',9:'VOUT2',10:'FB',11:'AGND',12:'RT',13:'PG',14:'EN/SYNC',15:'NC',16:'VIN2',17:'PGND',18:'PGND',19:'PGND',20:'PGND'}

def definition(name):
    pins=[]
    for n in range(1,21):
        y=-20+(n-1)*2
        pins.append(f'(pin passive line (at 20 {y} 180) (length 5) (name "{N[n]}" (effects (font (size 1 1)))) (number "{n}" (effects (font (size 1 1)))))')
    return f'''(symbol "PiSXMeRevAClean:{name}" (pin_names (offset 0.8)) (exclude_from_sim no) (in_bom yes) (on_board yes)
 (property "Reference" "U" (at 0 -24 0) (effects (font (size 1 1))))
 (property "Value" "TPSM63606RDLR" (at 0 24 0) (effects (font (size 1 1))))
 (property "Footprint" "PiSXMeRevAClean:TPSM63606RDLR_RDL0020" (at 0 0 0) (effects (font (size 1 1)) (hide yes)))
 (symbol "{name}_1_1" (rectangle (start -15 -22) (end 15 22) (stroke (width 0.254) (type default)) (fill (type background))) {' '.join(pins)}) (embedded_fonts no))'''

def replace(text,name,block):
    st=text.index(f'(symbol "PiSXMeRevAClean:{name}"'); old=balanced(text,st)
    return text[:st]+block+text[st+len(old):]

def main():
    s=P.read_text()
    for name in ('TPSM63606RDLR_5V','TPSM63606RDLR_3V3','TPSM63606RDLR_1V1'):
        s=replace(s,name,definition(name))
    # Remove the previous four-label scaffold rows; the probe supplies one
    # explicit label for every package pin instead.
    lines=[]
    for line in s.splitlines(True):
        if line.startswith('(label ') and '(at 70 ' in line and any(f'"{x}"' in line for x in ('12V_PROTECTED','CM5_5V','BRIDGE_3V3','BRIDGE_1V1','POWER_GND','POWER_PG_FAULT','BRIDGE_ENABLE')):
            continue
        lines.append(line)
    s=''.join(lines)
    start=s.index('  (sheet_instances ')
    labels=[]
    for i,(ref,y,rail) in enumerate((('U3',95,'CM5_5V'),('U4',95,'BRIDGE_3V3'),('U5',95,'BRIDGE_1V1'))):
        nets={1:'12V_PROTECTED',2:f'SW_{rail}',3:f'CBOOT_{rail}',4:f'RBOOT_{rail}',5:rail,6:'POWER_GND',7:'VCC_INTERNAL',8:rail,9:rail,10:f'FB_{rail}',11:'POWER_GND',12:f'RT_{rail}',13:f'PG_{rail}',14:'12V_PROTECTED',15:'NC',16:'12V_PROTECTED',17:'POWER_GND',18:'POWER_GND',19:'POWER_GND',20:'POWER_GND'}
        for n in range(1,21):
            py=y-(-20+(n-1)*2)
            labels.append(f'(label "{nets[n]}" (at 70 {py} 0) (effects (font (size 1.0 1.0)) (justify left)) (uuid 0a000000-0000-{i:04x}-0000-{n:012x}))\n')
    s=s[:start]+''.join(labels)+s[start:]
    P.write_text(s)
    print('TPSM right-facing native pin probe applied')
if __name__=='__main__': main()
